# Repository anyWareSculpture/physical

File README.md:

# physical
Physical computing aspects of anyWare (firmware, electronics)

## arduino

The Arduino sketches share some common code.
However, there are no good mechanism for sharing code when using the IDE.

Our workaround for now is to keep shared code in the common/ folder
and copy the files from there into each sketch folder.
Not nice, but the result is self-contained sketches.

We use the Teensy 3.x for parts of the system. Download the Teensyduino add-on from here: https://www.pjrc.com/teensy/td_download.html
Note: We don't need any libraries installed with Teensy as we include our own.

Note: As of December 2015, our code doesn't compile with Arduino >= 1.6.6.

### Programming Info

**PanelInterface:**

The 3 panel interfaces run off separate Arduinos running the same sketch, but with different configurations.

* Open PanelInterface/configuration.h
* Enable the controller you want to program; A, B or C
* Compile & Upload
* Repeat for all controllers

### Test sketches

These are just for hardware testing

### Test games

These are basic self-contained game sketches, for playtesting in isolation

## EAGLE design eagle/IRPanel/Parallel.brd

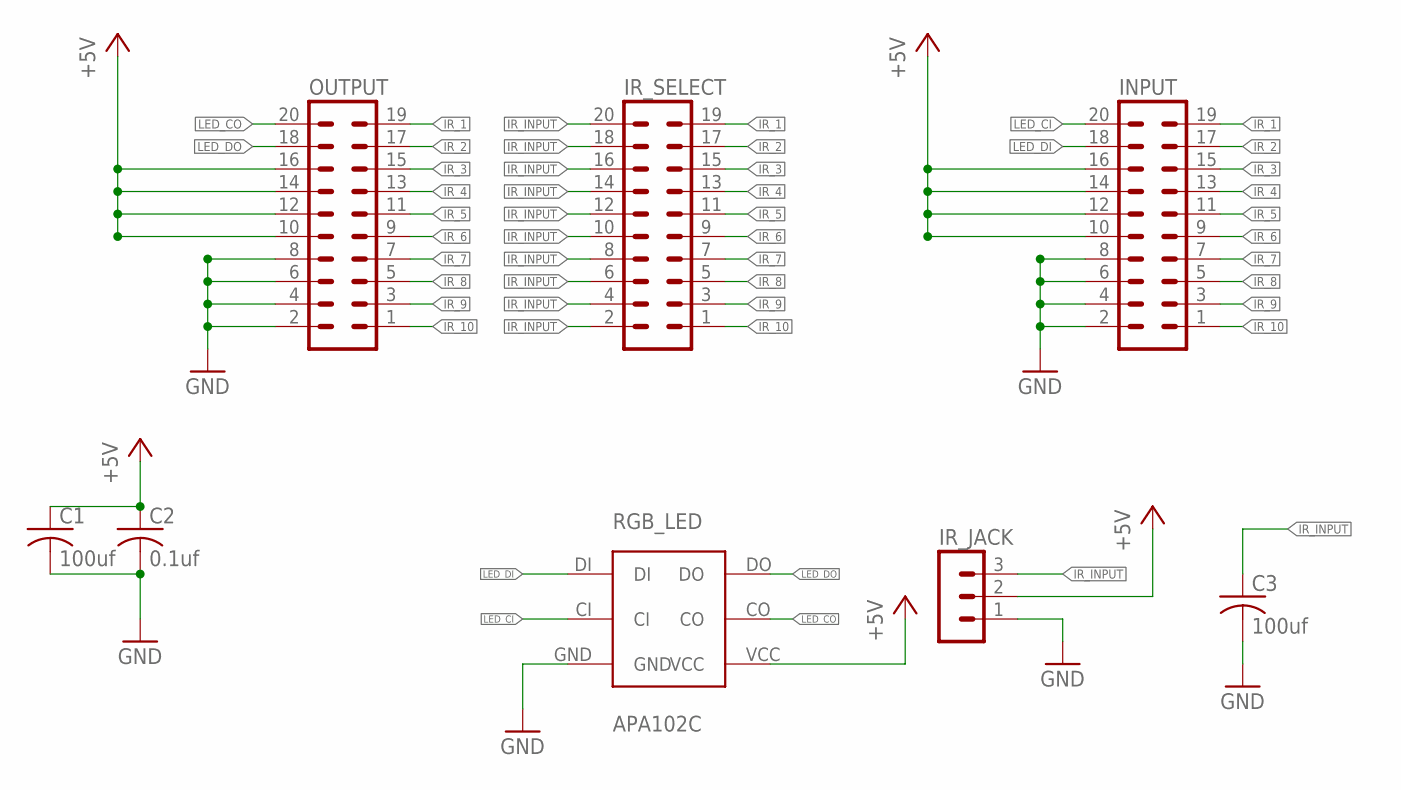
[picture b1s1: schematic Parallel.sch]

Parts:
C1, C3: 100uf; C0805
C2: 0.1uf; C0603
INPUT: MA10-2
IR_JACK: MA03-1
IR_SELECT: MA10-2
OUTPUT: MA10-2
RGB_LED: APA102C

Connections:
+5V: C1.1, C2.1, INPUT.10, INPUT.12, INPUT.14, INPUT.16, IR_JACK.2, OUTPUT.10, OUTPUT.12, OUTPUT.14, OUTPUT.16, RGB_LED.VCC
GND: C1.2, C2.2, C3.2, INPUT.2, INPUT.4, INPUT.6, INPUT.8, IR_JACK.1, OUTPUT.2, OUTPUT.4, OUTPUT.6, OUTPUT.8, RGB_LED.GND
IR_1: INPUT.19, IR_SELECT.19, OUTPUT.19
IR_2: INPUT.17, IR_SELECT.17, OUTPUT.17
IR_3: INPUT.15, IR_SELECT.15, OUTPUT.15
IR_4: INPUT.13, IR_SELECT.13, OUTPUT.13
IR_5: INPUT.11, IR_SELECT.11, OUTPUT.11
IR_6: INPUT.9, IR_SELECT.9, OUTPUT.9
IR_7: INPUT.7, IR_SELECT.7, OUTPUT.7
IR_8: INPUT.5, IR_SELECT.5, OUTPUT.5
IR_9: INPUT.3, IR_SELECT.3, OUTPUT.3
IR_10: INPUT.1, IR_SELECT.1, OUTPUT.1
IR_INPUT: C3.1, IR_JACK.3, IR_SELECT.2, IR_SELECT.4, IR_SELECT.6, IR_SELECT.8, IR_SELECT.10, IR_SELECT.12, IR_SELECT.14, IR_SELECT.16, IR_SELECT.18, IR_SELECT.20
LED_CI: INPUT.20, RGB_LED.CI
LED_CO: OUTPUT.20, RGB_LED.CO
LED_DI: INPUT.18, RGB_LED.DI
LED_DO: OUTPUT.18, RGB_LED.DO

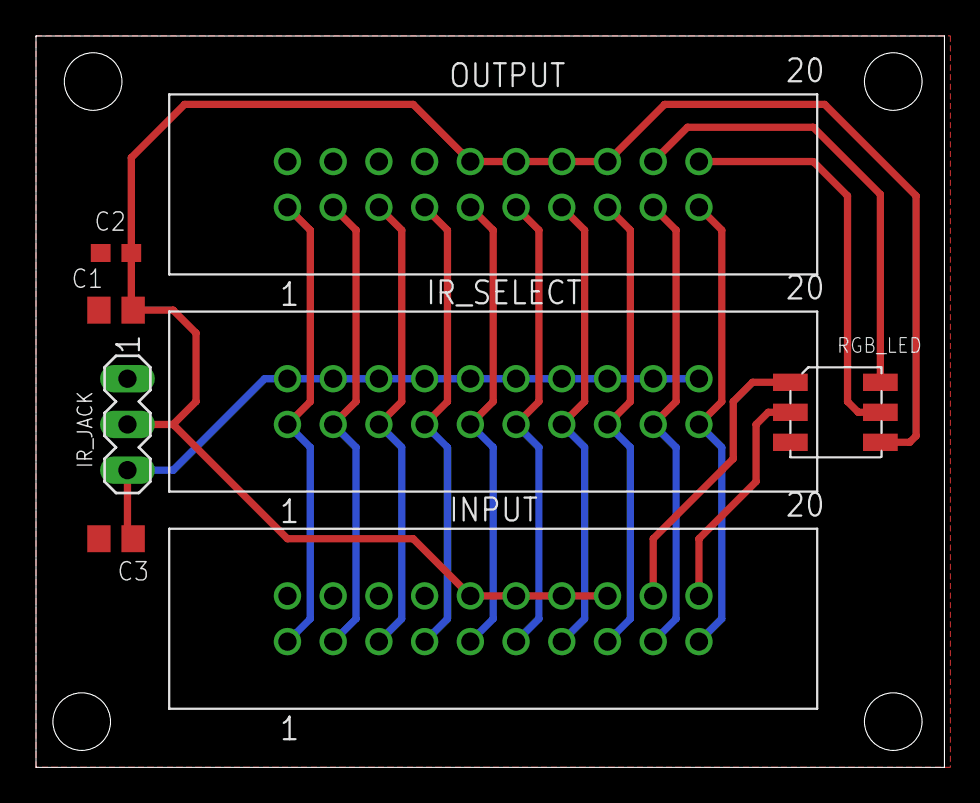
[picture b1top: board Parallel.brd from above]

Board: 2 copper layers, 50.5 x 40.6 mm, 8 parts (0 on the bottom side), 17 nets.

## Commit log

2015-05-31 Initial commit of knocking and handshake sketch. Untested.
2015-05-31 Added optional strength argument for knocking
2015-05-31 More debug output, Added support for ECHO
2015-06-04 Added buzzer on EXIT knock, print message on unknown INIT command
2015-06-04 Write newline before HELLO to avoid garbage
2015-06-13 Implemented the new serial protocol
2015-06-14 Reorganized to make sharing of code easier
2015-06-14 Initial implementation of disk game
2015-06-14 Moved global_stat and global_debug to anyware_global
2015-06-14 Initial implementation of simon game
2015-06-14 Minor refactoring
2015-06-14 Require Arduino Mega
2015-06-17 Test sketch for Simon (IR + Neopixel) modules
2015-06-18 No need for INVERT_STATE - both modules now behave the same way
2015-06-18 Moved from playground, tweaked and inlined libraries
2015-06-18 Initial implementation of the Panel interface
2015-06-18 readme
2015-06-21 Initial implementation of the handshake interface. Not tested
2015-06-22 Common code
2015-06-22 Added FIXME's for easings
2015-06-22 Initial implementation of asynchronous easing
2015-06-22 sync
2015-06-29 Synced with common
2015-06-29 Renamed to DiskInterface
2015-06-29 Refactored, added SUPPORTED
2015-06-29 Implemented updated serial protocol
2015-06-29 cosmetics
2015-06-29 Support per-pixel intensity
2015-06-29 NeoPixel ring (strip 4) now works
2015-06-29 Better debug output
2015-06-29 Added FIXMEs
2015-06-29 Validate userid for IDENTITY command
2015-06-29 Implemented easing for RGB LEDs
2015-06-29 Moved from playground
2015-06-29 PANEL_INIT -> INIT, Added binary pulse, increased serial buffer size
2015-06-29 DISK-INIT -> INIT
2015-08-29 Moved error functions to separate files
2015-08-29 Added new Sharp IR sensor
2015-08-29 Replaced NeoPixels with APA102 DotStar LEDS using FastLED library
2015-08-29 Ported to new Sharp sensors and FastLED library
2015-08-29 Moved old PanelInterface to old/
2015-08-29 Ported to new LEDs and new Sharp sensors
2015-08-29 SimonTester for old hardware
2015-08-30 Reintroduced debounding of Sharp sensors to work around sensitivity issues
2015-08-30 bugfix: APA102 requires end boundary to be written
2015-08-30 Bounce library
2015-08-30 Updated pinout to not conflict with FastLED SPI pins
2015-09-13 Rewrite LED and sensor interfaces to allow for more strips per controller, and separated sensors from leds as some strips will not have built-in sensors
2015-09-13 Ported to new LED and sensor interface
2015-09-14 Updated to new disk hardware
2015-09-14 Require Teensy 3.1
2015-09-14 Added test sketch for handshake interface
2015-09-14 Mockup of HandshakeInterface. Not tested
2015-09-14 Added TouchSensor class
2015-09-14 Added BLUE
2015-09-14 Added printCommand()
2015-09-14 bugfix: missing space in regexp
2015-09-14 Added printCommand(), sync
2015-09-14 Moved away old code
2015-09-20 Removed the G
2015-09-20 Removed debug lines
2015-09-20 Made stripId sepecification in controller configuration generic
2015-09-20 Mixed up strip 3 and 4
2015-09-20 Ticks per revolutions are unique to each disk
2015-09-26 Disabled debug output
2015-09-26 Added configs for all three controllers
2015-09-26 TouchSensor doesn't (yet) belong in common due to compilation issues with the Wire library
2015-09-26 Deprecated IDENTITY, INIT and RESET, introduced HELLO command
2015-09-26 Minor improvement to the blackout timing
2015-09-26 Added 4th LED to strip, fixed colorwipe
2015-11-27 ignore /tmp
2015-11-27 ignore more stuff
2015-11-27 Added note about Teensy
2015-11-27 Introduced BLOCKED state to avoid output of positions during homing
2015-11-27 Sculpture-centric order of LED strip
2015-11-27 Don't touch perimeter LEDs
2015-11-27 Default to non-debug mode to reduce verbose output
2015-11-27 Added vibration and high-power LEDs
2015-11-27 Added 'sleep' easing
2015-11-28 Coding style: use this->
2015-11-29 Support duration of easings
2015-11-29 Adjusted sensitivity
2015-11-29 Better calibrated ticks per revolution
2015-12-22 FIXME
2015-12-22 Don't output HIT TICKS unless we're ready and moving, to avoid noisy serial output
2016-06-13 Prepare for new DiskInterface - copy of old DiskInterface
2016-06-13 Removed panel commands and LED control
2016-06-13 How to program panel interfaces
2016-06-13 Updated to use new disk sensors; ring of IR steps rather than a single hall effect sensor
2016-06-14 Added strip 3 from the disk interface to the handshake interface
2016-06-14 Ignore pos/dir commands while homing, as this could put the interface into an unusable state (stop while homing)
2016-09-02 IR panel design from Mo
2016-11-14 Updated configuration to new board design
2016-11-19 Added IR Panel Shield schematics
2016-11-19 Added handshake schematics
2016-11-23 Simple sketch to test all high power LEDs in ON state
2016-11-23 Updated to actually built hardware
2016-11-28 Minimal RGB Strip test
2016-12-10 Print warning if wrong MCU is selected
2016-12-10 Switch LED pins, print warning if wrong MCU is selected
2016-12-10 Added HandshakeDebugger
2016-12-10 New test sketch testing both high power LEDs and RGB stips
2017-01-26 Adjusted to new physical configuration, print active panel IDs
2017-01-26 Default to no-debug mode
2017-01-26 Adjusted to new physical configuration
2017-01-26 New handshake sensitivity setting
2017-02-09 RGB strip tuning sketch. Needs testing.
2017-02-09 Added soft shutdown scripts
2017-02-09 Debounced shutdown button
2017-02-10 Schematic for soft power button
2017-02-10 Moved to its own folder
2017-02-13 Show version number on HELLO
2017-02-13 Added support for color state RGB strips
2017-02-13 Renamed user0-2 to sculpture1-3
2017-02-13 typo
2017-02-14 doc fix
2017-02-18 Added real RGB strip colors
2017-02-18 Bugfix: Respect intensity for RGB strip. V1.2.1
2017-02-25 Desktop background
2017-04-16 Added anyware service script
2017-05-07 New splash screens
2017-05-07 Raspberry startup scripts
2017-06-18 Synchronize common physical API
2017-06-18 New yellow location color
2018-04-22 Support double-click to reboot
2018-05-26 Bugfix: Change of color during fade caused the LED to turn blue
2018-05-26 more debug commands
2018-05-27 V1.3
2018-05-27 V1.2
2018-06-10 Removed unused global_state
2018-06-10 Removed PANEL-ANIMATE and PANEL-STATE commands
2018-06-10 Added support for specifying multiple panels to PANEL-SET and PANEL-PULSE
2018-06-10 Simplified configuration specification
2018-06-10 Use STRIP_LEDS instead of hardcoded 10
2018-06-10 Bugfix for virtual light
